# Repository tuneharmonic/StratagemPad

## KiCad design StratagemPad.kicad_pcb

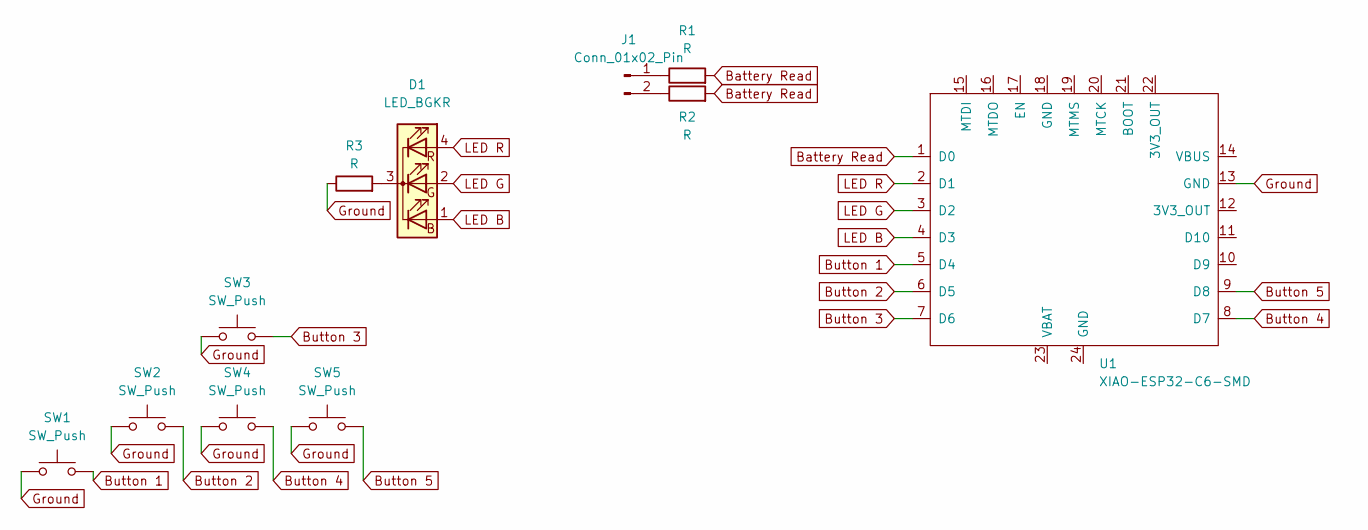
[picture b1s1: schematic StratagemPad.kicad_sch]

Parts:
D1: LED_BGKR; LED_D5.0mm-4_RGB_Wide_Pins
J1: Conn_01x02_Pin; JST_PH_B2B-PH-K_1x02_P2.00mm_Vertical
R1, R2, R3: R; R_Axial_DIN0204_L3.6mm_D1.6mm_P2.54mm_Vertical
SW1: SW_Push; SW_Hotswap_Kailh_MX_1.50u_90deg
SW2, SW3, SW4, SW5: SW_Push; SW_Hotswap_Kailh_MX_1.00u
U1: XIAO-ESP32-C6-SMD; XIAO-ESP32-C6-DIP

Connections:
Battery Read: R1.2, R2.2, U1.1 (D0)
Button 1: SW1.2, U1.5 (D4)
Button 2: SW2.2, U1.6 (D5)
Button 3: SW3.2, U1.7 (D6)
Button 4: SW4.2, U1.8 (D7)
Button 5: SW5.2, U1.9 (D8)
Ground: R3.1, SW1.1, SW2.1, SW3.1, SW4.1, SW5.1, U1.13 (GND)
LED B: D1.1 (BA), U1.4 (D3)
LED G: D1.2 (GA), U1.3 (D2)
LED R: D1.4 (RA), U1.2 (D1)
unnamed: D1.3 (K), R3.2
unnamed: J1.1, R1.1
unnamed: J1.2, R2.1

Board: 2 copper layers, 11 parts (0 on the bottom side), 13 nets, no tracks yet.
